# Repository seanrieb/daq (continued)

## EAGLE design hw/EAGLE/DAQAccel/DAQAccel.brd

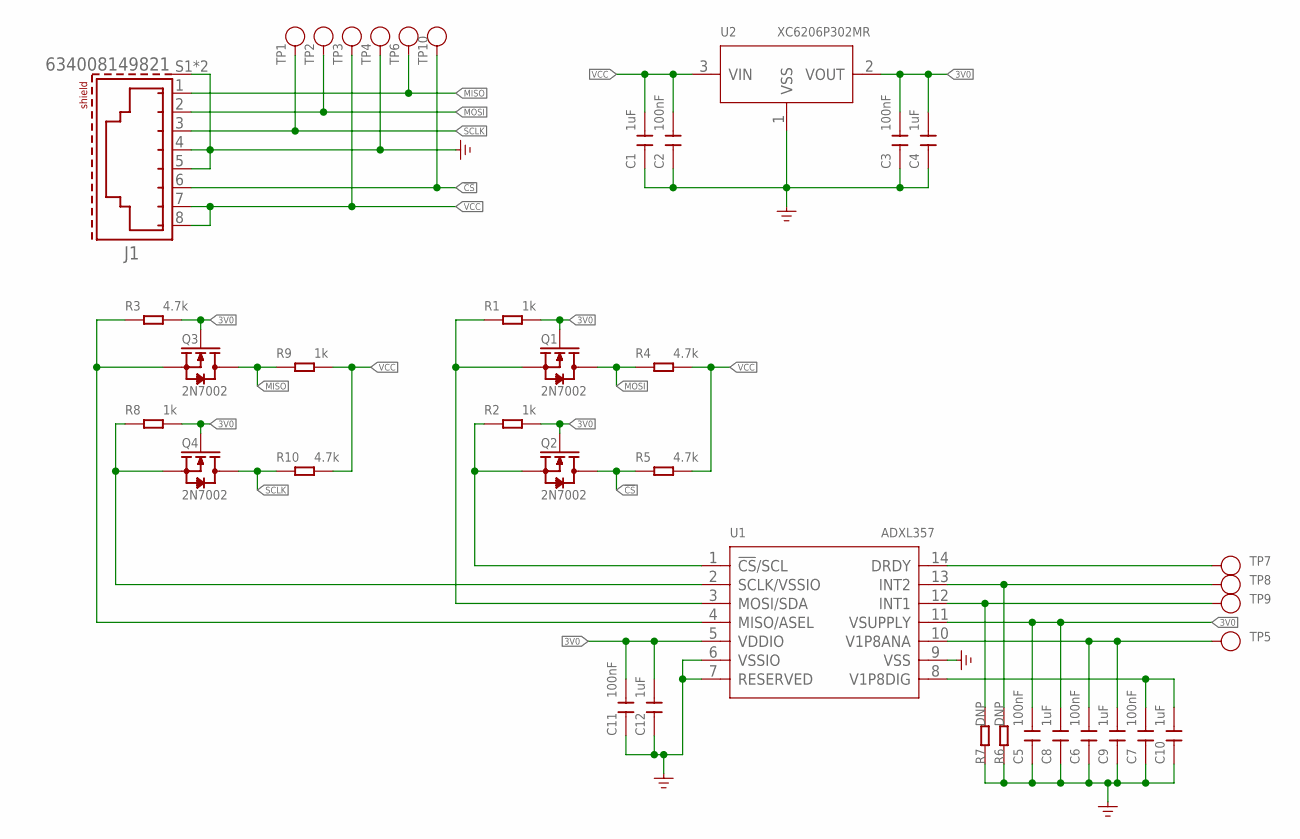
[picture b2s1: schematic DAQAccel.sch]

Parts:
C1, C4, C8, C9, C10, C12: 1uF; C0603
C2, C3, C5, C6, C7, C11: 100nF; C0603
J1: 634008149821
Q1, Q2, Q3, Q4: 2N7002; SOT-23
R1, R2, R8, R9: 1k; R0603
R3, R4, R5, R10: 4.7k; R0603
R6, R7: DNP; R0603
TP1, TP2, TP3, TP4, TP5, TP6, TP7, TP8, TP9, TP10: Test; TP-D45MIL
U1: ADXL357; LCC-14-TERMINAL
U2: XC6206P302MR; SOT-23

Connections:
3V0: C3.2, C4.2, C5.2, C8.2, C11.2, C12.2, Q1.1 (G), Q2.1 (G), Q3.1 (G), Q4.1 (G), R1.2, R2.2, R3.2, R8.2, U1.5 (VDDIO), U1.11 (VSUPPLY), U2.2 (VOUT)
!CS: J1.6, Q2.3 (D), R5.1, TP10.T
GND: C1.1, C2.1, C3.1, C4.1, C5.1, C6.1, C7.1, C8.1, C9.1, C10.1, C11.1, C12.1, J1.4, J1.5, J1.S1 (SHIELD), J1.S2 (SHIELD), R6.1, R7.1, TP4.T, U1.6 (VSSIO), U1.7 (RESERVED), U1.9 (VSS), U2.1 (VSS)
MISO: J1.1, Q3.3 (D), R9.1, TP6.T
MOSI: J1.2, Q1.3 (D), R4.1, TP2.T
unnamed: Q2.2 (S), R2.1, U1.1 (!CS!/SCL)
unnamed: TP7.T, U1.14 (DRDY)
unnamed: Q1.2 (S), R1.1, U1.3 (MOSI/SDA)
unnamed: R6.2, TP8.T, U1.13 (INT2)
unnamed: C6.2, C9.2, TP5.T, U1.10 (V1P8ANA)
unnamed: Q4.2 (S), R8.1, U1.2 (SCLK/VSSIO)
unnamed: C7.2, C10.2, U1.8 (V1P8DIG)
unnamed: R7.2, TP9.T, U1.12 (INT1)
unnamed: Q3.2 (S), R3.1, U1.4 (MISO/ASEL)
SCLK: J1.3, Q4.3 (D), R10.1, TP1.T
VCC: C1.2, C2.2, J1.7, J1.8, R4.2, R5.2, R9.2, R10.2, TP3.T, U2.3 (VIN)

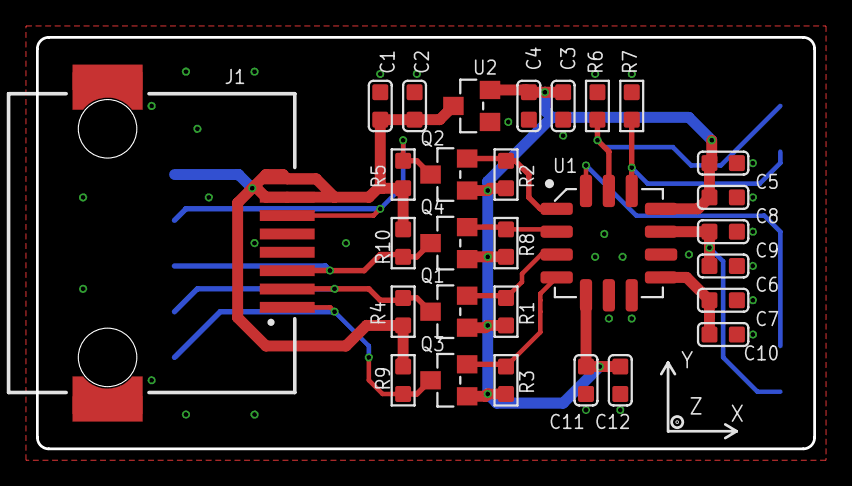
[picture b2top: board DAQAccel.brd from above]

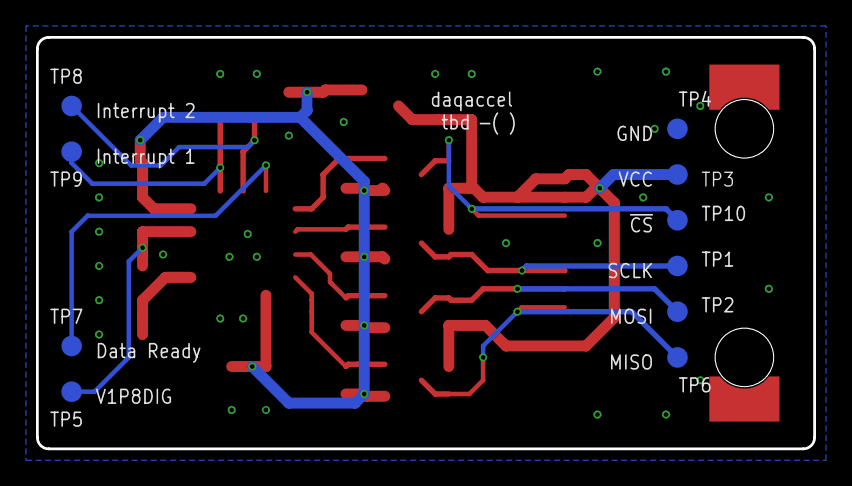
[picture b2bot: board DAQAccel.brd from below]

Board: 2 copper layers, 43.2 x 22.9 mm, 39 parts (10 on the bottom side), 16 nets.

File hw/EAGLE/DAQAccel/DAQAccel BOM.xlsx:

Qty | Onhand | Vendor | Vendor P/N | Value | Device | Package | Parts | Description
6 | 15 | Mouser | 710-885382206004 | 100nF | CAP-0603 | C0603 | C2, C3, C5, C6, C7, C11 | Ceramic Capacitors
6 | 0 | Mouser | 187-CL10B105KA8NNNC | 1uF | CAP-0603 | C0603 | C1, C4, C8, C9, C10, C12 | Ceramic Capacitors
4 | 12 | Mouser | 512-2N7002L | 2N7002 | MOSFET-N'SOT23' | SOT-23 | Q1, Q2, Q3, Q4 | IRLL014:
8 | 3 | Mouser | 660-RK73B1JTTDD472J | 4.7k | RES-0603 | R0603 | R1, R2, R3, R4, R5, R8, R9, R10
1 | 0 | Mouser | 710-634008149821 | 634008149821 | 634008149821 | 634008149821 | J1 | WR-MJ Modular Jack Horizontal Shielded SMT 8P8C Tab Up
1 |  |  |  | ADXL357 | SENSOR-ADXL357BEZ | LCC-14-TERMINAL | U1
2 |  |  |  | DNP | RES-0603 | R0603 | R6, R7
10 |  |  |  | Test | TEST-POINT'4545' | TP-D45MIL | TP1, TP2, TP3, TP4, TP5, TP6, TP7, TP8, TP9, TP10
1 | 1 | Mouser | 621-AP2125N-3.0TRG1 | XC6206P302MR | PMIC-XC6206PMR | SOT-23 | U2 | LOW ESR Cap.Compatible Positive Voltage Regulators

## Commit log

2025-09-15 Fixed typos Added defines to ADS
